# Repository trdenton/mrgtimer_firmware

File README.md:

# mrgtimer\_firmware
firmware for Manitoba Robot Games timer board

# Prerequisites

Use arduino 1.8... newer versions might work too

Install DFRobot LCD library.  In Arduino IDE, go to "Tools > Manage Libraries..."

Search for DFRobot LCD and install DFRobot\_RGBLCD1602 v2.0.0

# Directories

## old\_sketches/race\_timer

This is the original Arduino sketch by Bruce

## old\_sketches/mrg\_timer

This is some work done by Troy, wholly ignorant of the previous work done by Bruce

## mrgtimer\_firmware

This is the functioning sketch, a combination of the above two works

## kicad

board design files

# Compilation

open the mrgtimer\_firmware project in the arduino ide

this can be done with `make gui` (read the Makefile for instructions)

ensure the board type is set to 'Arduino Nano' (atmega328p variant)

# Compilation w/ arduino-cli

Install arduino cli
install avr core: ~/Software/arduino-cli core install arduino:avr
now you can use the following:
make verify
make upload

# Known Issues

Pins A6 and A7 cannot be used as outputs - these drive the finish lights

possible workaround: patch S0 and S1 to A6 and A7 respectively, drive those pins instead.
would lose SPI ability though.

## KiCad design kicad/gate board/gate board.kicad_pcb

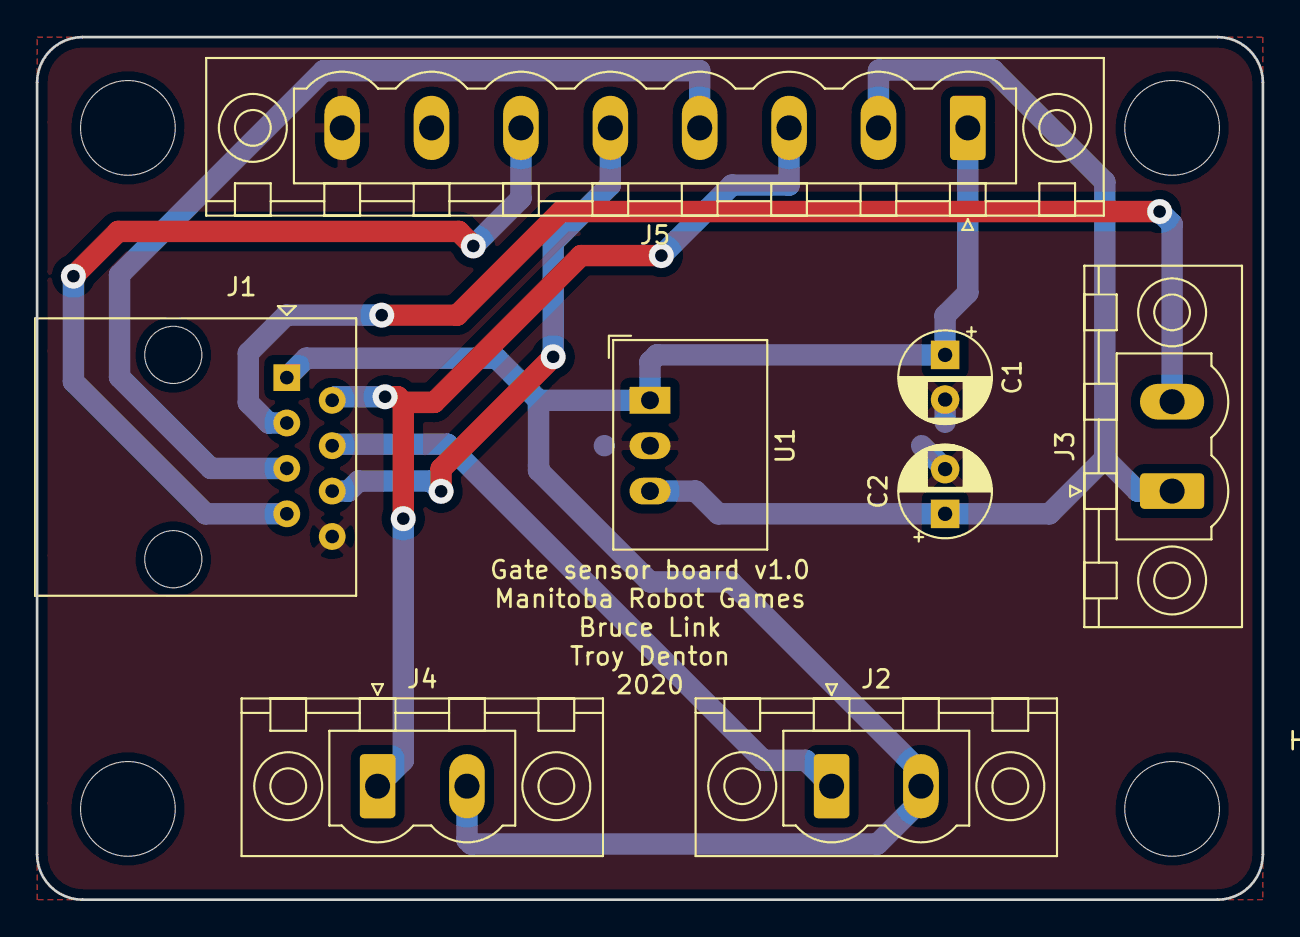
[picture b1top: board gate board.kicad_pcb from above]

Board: 2 copper layers, 68.6 x 48.3 mm, 12 parts (0 on the bottom side), 9 nets.

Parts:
C1: 1000uF; CP_Radial_D5.0mm_P2.50mm
C2: 100uF; CP_Radial_D5.0mm_P2.50mm
HOLE1, HOLE2, HOLE3, HOLE4: MountingHole_5.3mm_M5
J1: 8P8C; RJ45_Amphenol_54602-x08_Horizontal
J2: beam excite; PhoenixContact_MSTBV_2,5_2-GF_1x02_P5.00mm_Vertical_Threade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
J3: beam detect; PhoenixContact_MSTBV_2,5_2-GF_1x02_P5.00mm_Vertical_Threade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
J4: light; PhoenixContact_MSTBV_2,5_2-GF_1x02_P5.00mm_Vertical_Threade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
J5: Board; PhoenixContact_MSTBV_2,5_8-GF_1x08_P5.00mm_Vertical_Threade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
U1: R-78E5.0-0.5; Converter_DCDC_RECOM_R-78E-0.5_THT

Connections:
+5V: C2.1, J3.1, J5.2, U1.3
+12V: C1.1, J1.1, J2.2, J4.2, J5.1, U1.1
/CLK: J1.7, J5.6
/SERA: J1.6, J5.5
/beam_detect: J1.3, J3.2
/beam_excite: J1.4, J2.1
/chipsel: J1.5, J5.4
/start_light: J1.2, J4.1, J5.3
GND: C1.2, C2.2, J1.8, J5.8, U1.2

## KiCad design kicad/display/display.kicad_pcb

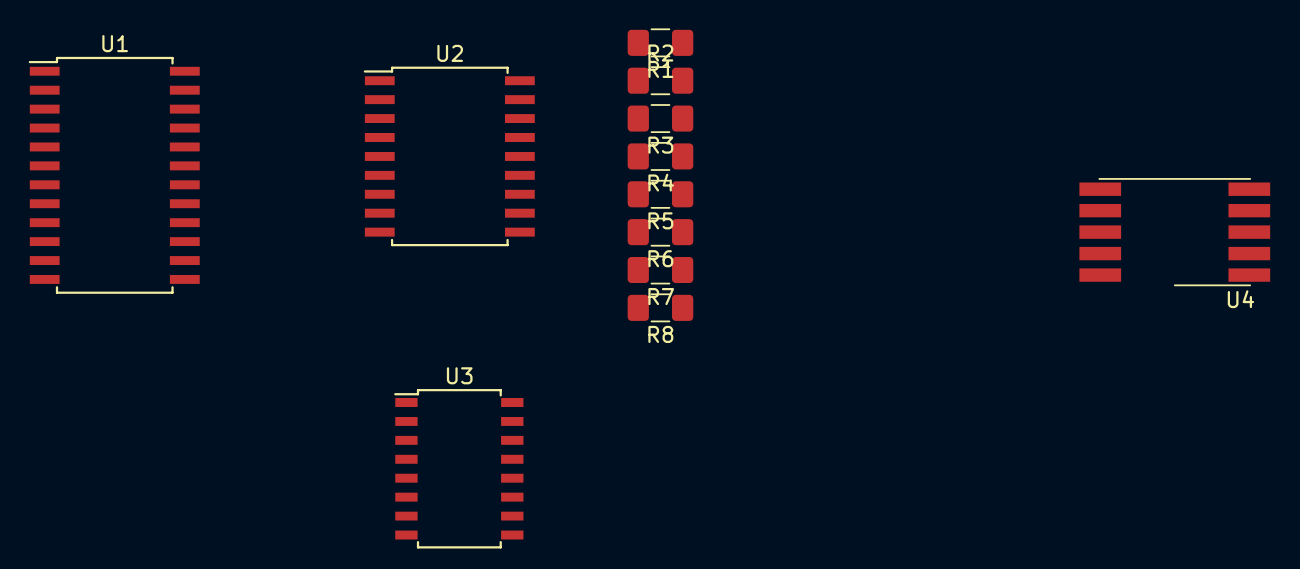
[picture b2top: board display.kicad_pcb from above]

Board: 2 copper layers, 12 parts (0 on the bottom side), 28 nets, no tracks yet.

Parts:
R1, R2, R3, R4, R5, R6, R7, R8: R; R_1206_3216Metric_Pad1.42x1.75mm_HandSolder
U1: MAX7219; SOIC-24W_7.5x15.4mm_P1.27mm
U2: TBD62783A-NPN; SOIC-18W_7.5x11.6mm_P1.27mm
U3: SN75374D; SOIC-16W_5.3x10.2mm_P1.27mm
U4: KCSA02-105; KCSC02-105

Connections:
+5V: U1.19, U3.16
+12V: U2.9, U3.1, U3.9
GND: U1.4, U1.9, U2.10, U3.8
unnamed: R1.1, U4.7
unnamed: R1.2, U2.18
unnamed: R2.1, U4.6
unnamed: R2.2, U2.17
unnamed: R3.1, U4.4
unnamed: R3.2, U2.16
unnamed: R4.1, U4.2
unnamed: R4.2, U2.15
unnamed: R5.1, U4.1
unnamed: R5.2, U2.14
unnamed: R6.1, U4.9
unnamed: R6.2, U2.13
unnamed: R7.1, U4.10
unnamed: R7.2, U2.12
unnamed: R8.1, U4.5
unnamed: R8.2, U2.11
unnamed: U1.14, U2.1
unnamed: U1.15, U2.6
unnamed: U1.16, U2.2
unnamed: U1.17, U2.7
unnamed: U1.20, U2.3
unnamed: U1.21, U2.5
unnamed: U1.22, U2.8
unnamed: U1.23, U2.4
unnamed: U4.3, U4.8

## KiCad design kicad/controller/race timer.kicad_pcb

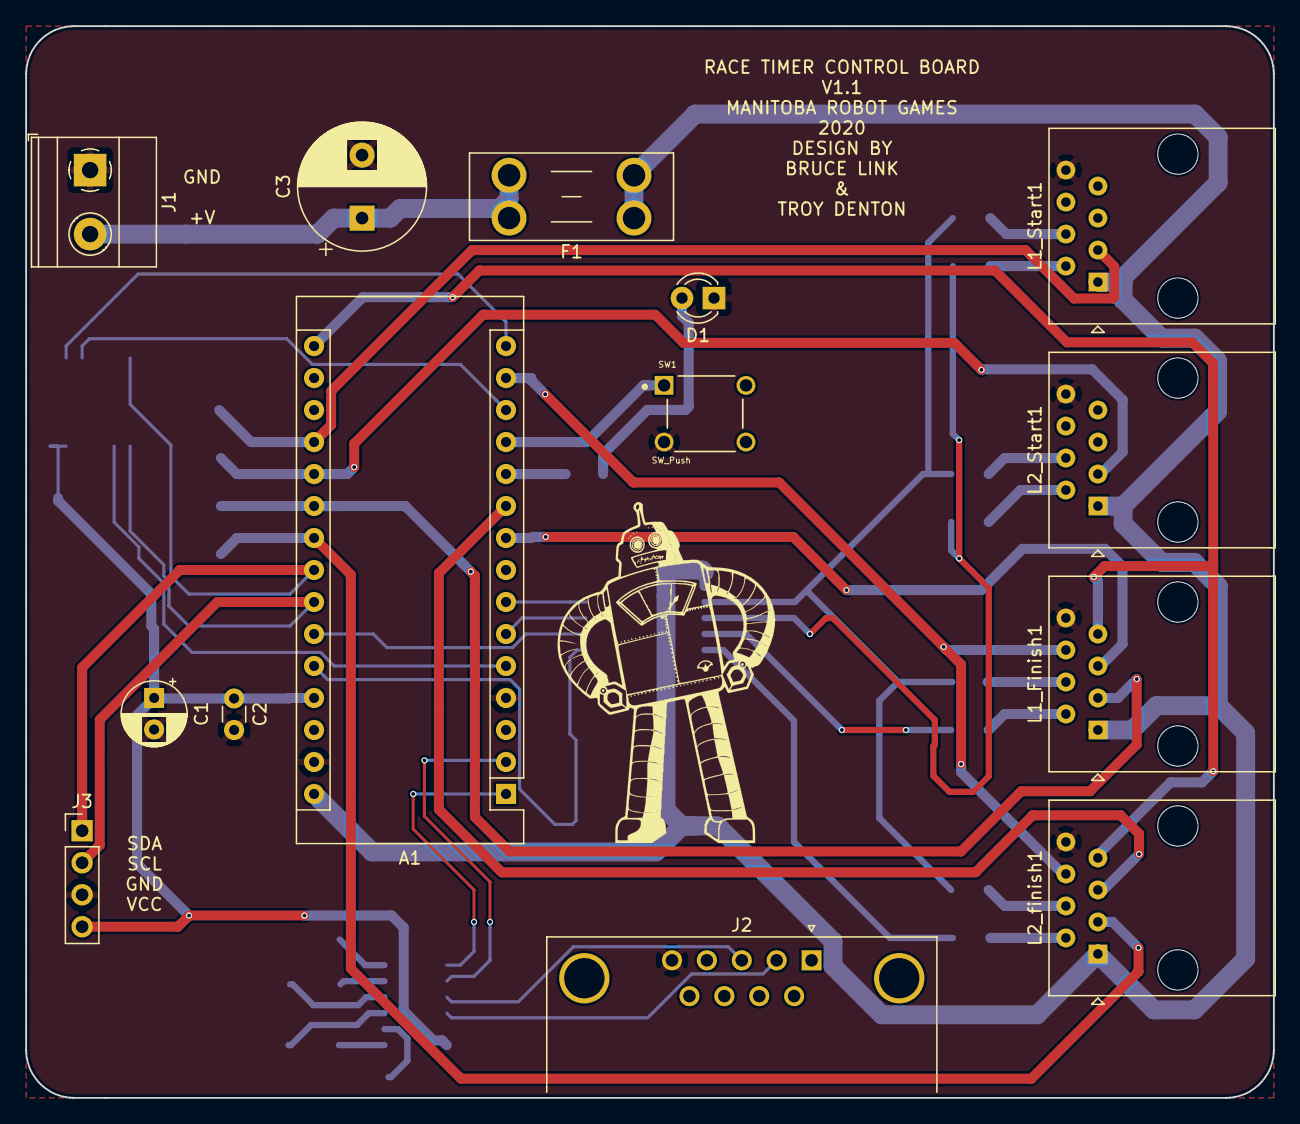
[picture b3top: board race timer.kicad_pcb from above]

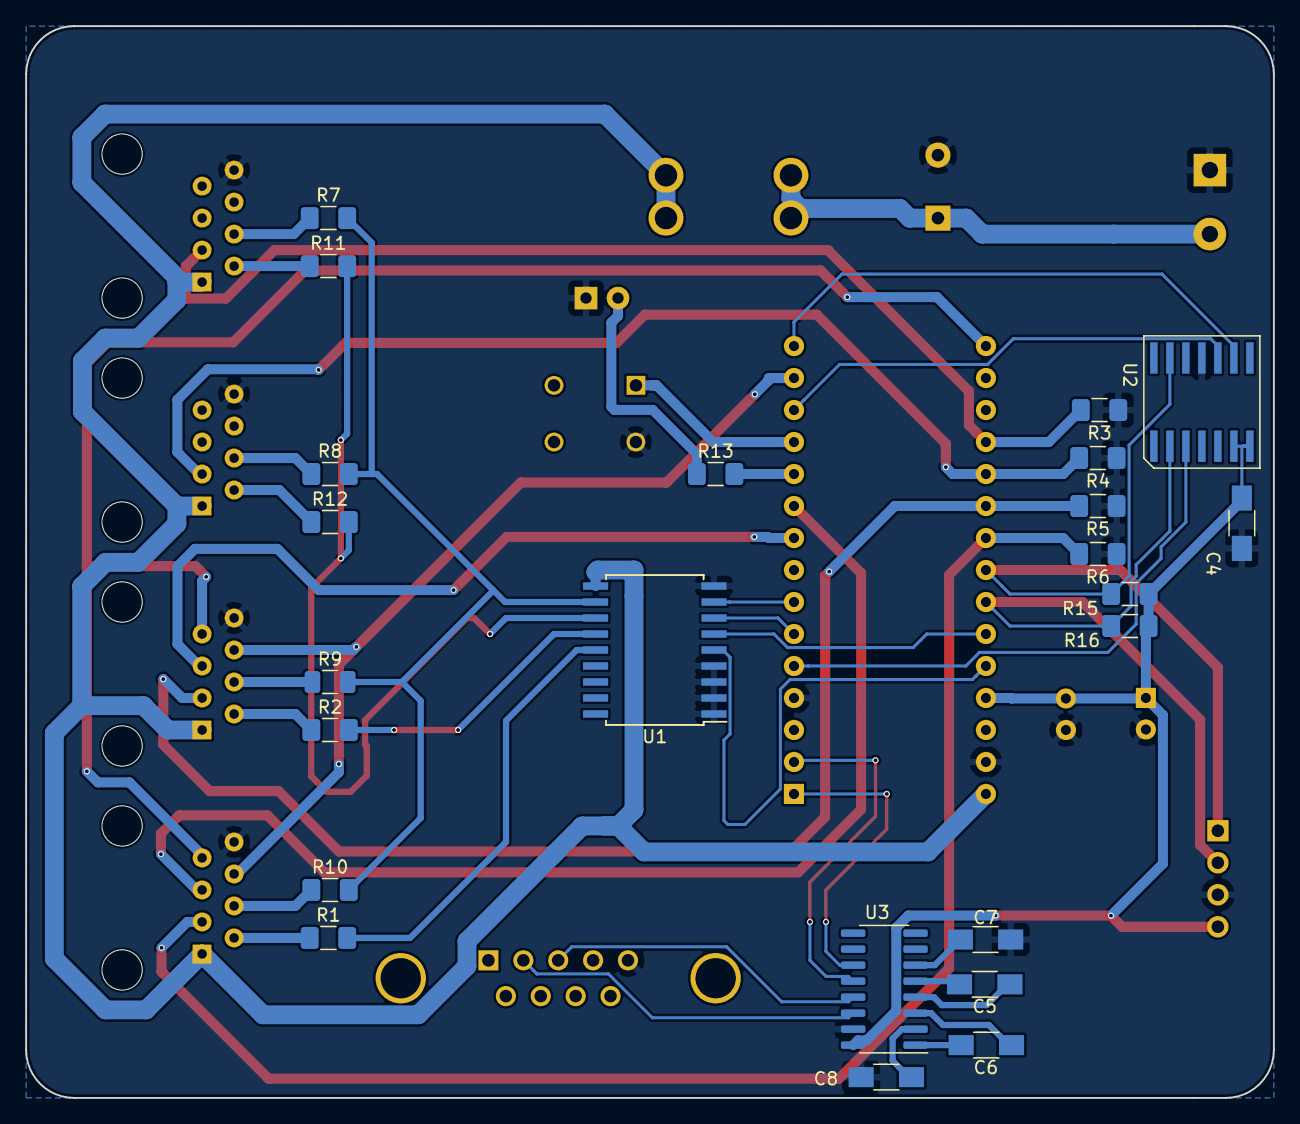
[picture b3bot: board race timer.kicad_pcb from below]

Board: 2 copper layers, 99.1 x 85.1 mm, 37 parts (23 on the bottom side), 46 nets.

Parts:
A1: Arduino_Nano_v3.x; Arduino_Nano
C1: CP1; CP_Radial_D5.0mm_P2.50mm
C2: C; C_Disc_D3.0mm_W1.6mm_P2.50mm
C3: CP1; CP_Radial_D10.0mm_P5.00mm
C4, C5, C6, C7, C8: 1uF; C_1206_HandSoldering
D1: LED; LED_D3.0mm
F1: Fuse; Fuseholder_Blade_Mini_Keystone_3568
J1: Screw_Terminal_01x02; TerminalBlock_Phoenix_MKDS-1,5-2-5.08_1x02_P5.08mm_Horizont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
J2: DB9_Female; DSUB-9_Female_Horizontal_P2.77x2.84mm_EdgePinOffset7.70mm_H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
J3: Conn_01x04; PinHeader_1x04_P2.54mm_Vertical
L1_Finish1, L1_Start1, L2_Start1, L2_finish1: 8P8C; RJ45_Amphenol_54602-x08_Horizontal
R1, R2, R11, R12, R13: 470; R_1206_3216Metric_Pad1.42x1.75mm_HandSolder
R3, R4, R5: 130K; R_1206_3216Metric_Pad1.42x1.75mm_HandSolder
R6: 130k; R_1206_3216Metric_Pad1.42x1.75mm_HandSolder
R7, R8, R10: 150; R_1206_3216Metric_Pad1.42x1.75mm_HandSolder
R9: 150; R_1206_3216Metric
R15, R16: 10K; R_1206_3216Metric_Pad1.42x1.75mm_HandSolder
SW1: SW_Push; SW_2-1825910-7
U1: ULN2803A; SOIC-18W_7.5x11.6mm_P1.27mm
U2: RX-8803SA; SOIC-14
U3: MAX232N; SOIC-16_3.9x9.9mm_P1.27mm

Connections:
+12V: C3.1, F1.2, J1.2
/5V: A1.27, C1.1, C2.1, C4.1, J3.4, R15.1, R16.1, U2.6, U2.7, U3.16
/12V_FUSED: A1.30, F1.1, L1_Finish1.1, L1_Start1.1, L2_Start1.1, L2_finish1.1, U1.10
/D1: A1.26, U1.5
/D2: A1.25, U1.6
/D3: A1.6, U1.7
/D4: A1.7, U1.8
/EVIN: A1.15, U2.9
/FOUT: A1.5, U2.3
/I2C_SCL: A1.24, J3.2, R16.2, U2.2
/I2C_SDA: A1.23, J3.1, R15.2, U2.13
/INT: A1.13, U2.10
/LED1: A1.11, R13.2
/MOSI: A1.14, L1_Finish1.6, L2_finish1.6
/PB1: A1.12, SW1.1
/PORT0_LED_EXCITE: L1_Start1.4, R7.1
/PORT1_LED_EXCITE: L2_Start1.4, R8.1
/PORT2_LED_EXCITE: L1_Finish1.4, R9.1
/PORT3_LED_EXCITE: L2_finish1.4, R10.1
/RX: A1.2, U3.12
/RXOUT: J2.3, U3.13
/SCL: A1.16, L1_Finish1.7, L2_finish1.7
/SEL0: A1.9, L1_Finish1.5
/SEL1: A1.10, L2_finish1.5
/TX: A1.1, U3.11
/TXOUT: J2.2, U3.14
GND: A1.4, A1.29, C1.2, C2.2, C3.2, C4.2, C7.2, C8.2, D1.1, J1.1, J2.5, J3.3, L1_Finish1.8, L1_Start1.8, L2_Start1.8, L2_finish1.8, R3.1, R4.1, R5.1, R6.1, SW1.2, U1.1, U1.2, U1.3, U1.4, U1.9, U2.11, U3.15
unnamed: A1.19, L1_Start1.3, R3.2
unnamed: A1.20, L2_Start1.3, R4.2
unnamed: A1.21, L1_Finish1.3, R5.2
unnamed: A1.22, L2_finish1.3, R6.2
unnamed: C5.1, U3.4
unnamed: C5.2, U3.5
unnamed: C6.1, U3.1
unnamed: C6.2, U3.3
unnamed: C7.1, U3.6
unnamed: C8.1, U3.2
unnamed: D1.2, R13.1
unnamed: L1_Finish1.2, R2.1
unnamed: L1_Start1.2, R11.1
unnamed: L2_Start1.2, R12.1
unnamed: L2_finish1.2, R1.1
unnamed: R1.2, U1.14
unnamed: R2.2, U1.13
unnamed: R7.2, R8.2, R9.2, R10.2, U1.11
unnamed: R11.2, R12.2, U1.12

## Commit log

2023-02-24 add Troy's initial state
2023-02-24 add in Bruce's original sketch + some readme content
2023-02-24 begin merging sketches
2023-02-24 start folding in other work, formatting
2023-02-24 Add a makefile
2023-02-24 add basic makefie
2023-02-24 move to .cpp for easier compile
2023-02-24 restructure, doc'n
2023-02-24 defines to enums
2023-02-24 add lcd functions
2023-02-24 remove debug comment, update gitignore
2023-02-25 use arduino-cli
2023-02-25 slight tweaks
2023-02-28 add kicad files
2023-02-28 max serial speed empirically
2023-02-28 cleanup state printing, add debug commands for timer, add WTF macro
2023-02-28 add term target for serial comms
2023-03-04 add gate board schematic
2023-03-04 update IO defs
2023-03-05 set up win lights
2023-03-05 add wine state logic
2023-03-05 add beams command
2023-03-05 add lcd test functions, fix time display
2023-03-05 fix millisecond output in serial debug
2023-03-08 fix lane 2 config, lcd display more messages, add sim target
2023-03-11 gate board mount models
2023-03-11 ensure extruded part of dovetail fitting is smaller than socket
2023-03-13 Updated push button logic
2023-03-15 updated .gitignore board bracket
2023-03-15 cal fail message persists. add sim_fw make target
2023-03-15 fix lcd_message str compare
2023-03-15 fit message on display for false start
2023-03-15 fix initial cal fail scenario
2023-03-15 elapsed time displayed during race
2023-03-15 add timer countdown to display
2023-03-15 only read ADC channels where needed. False start requires button press to proceed
2023-03-15 only read finish gate once start gate passed
2023-03-15 Added STATE_CALIBRATE_SETTLE state
2023-03-16 overhaul to detection routine.
2023-03-16 Slowed LCD update to 10hz
2023-03-16 LCD refresh time to 10Hz
2023-03-17 Fix to starting light logic.
2023-03-17 fix compile error, fix starter light
